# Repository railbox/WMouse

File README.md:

## Introduction
This is the Open Sourse WiFi DCC remote control for controlling turnouts and locomotives via command stations supporting Roco Z21 Wi-Fi protocol. 
The hardware is based on ESP8266 chip and ssd1106 based OLED.
The software is using Arduino IDE for output hex file building.
### Dependensies
The code dependant on ESP8266 library for Arduino IDE and Async UDP Library for ESP8266 Arduino.
### Helpers
There is a possibility to debug device menu using CodeBlocks IDE on the Windows. See Menu.cbp.

## Configuration
User should configure the default Wi-Fi net name and password in "src/config.h" file. See CL_SSID and CL_PASS defines.

## Hardware
The PCB project made in Kicad IDE could be fould under Mouse folder.
The PCB thickness is 1mm.
The case is borrowed from airconditioner remote control DG11J1-16 which could be found on aliexpress or ebay.

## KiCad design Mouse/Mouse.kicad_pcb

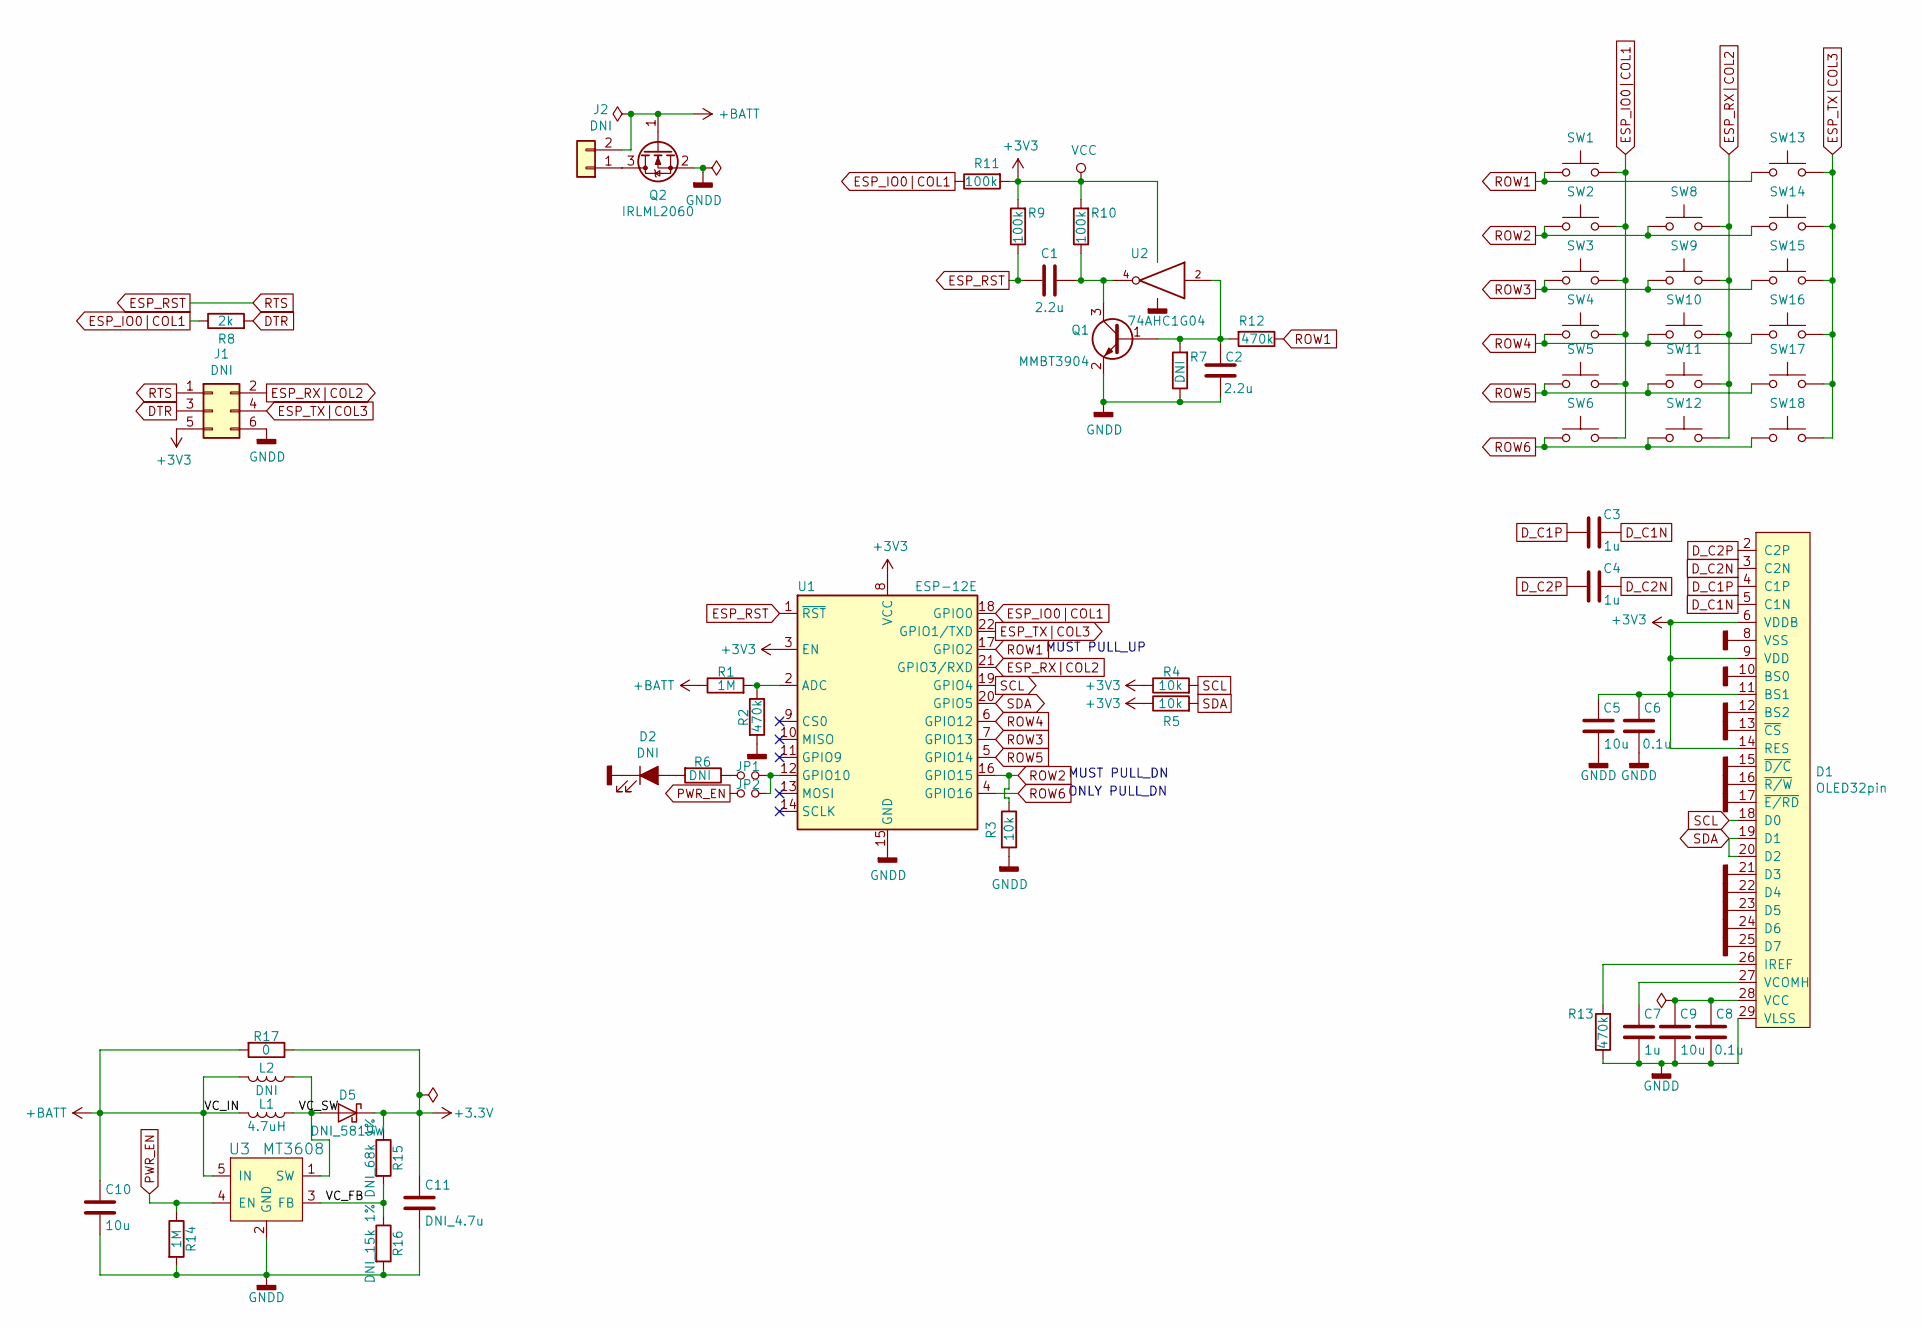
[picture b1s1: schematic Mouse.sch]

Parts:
C1, C2: 2.2u; C_0805_2012Metric_Pad1.15x1.40mm_HandSolder
C3, C4, C7: 1u; C_0805_2012Metric_Pad1.15x1.40mm_HandSolder
C5, C9, C10: 10u; C_0805_2012Metric_Pad1.15x1.40mm_HandSolder
C6, C8: 0.1u; C_0805_2012Metric_Pad1.15x1.40mm_HandSolder
C11: DNI_4.7u; C_0805_2012Metric_Pad1.15x1.40mm_HandSolder
D1: OLED32pin; OLED_32pin
D2: DNI; LED_D5.0mm_Horizontal_O3.81mm_Z3.0mm
D5: DNI_5819W; D_SOD-123
J1: DNI; PinHeader_2x03_P2.54mm_Vertical
J2: DNI; RC_case
JP1, JP2: DNI; SolderJumper-2_P1.3mm_Open_TrianglePad1.0x1.5mm
L1: 4.7uH; L_1210_3225Metric_Pad1.42x2.65mm_HandSolder
L2: DNI; L_1812_4532Metric
Q1: MMBT3904; SOT-23_Handsoldering
Q2: IRLML2060; SOT-23_Handsoldering
R1, R14: 1M; R_0805_2012Metric_Pad1.15x1.40mm_HandSolder
R2, R12, R13: 470k; R_0805_2012Metric_Pad1.15x1.40mm_HandSolder
R3, R4, R5: 10k; R_0805_2012Metric_Pad1.15x1.40mm_HandSolder
R6, R7: DNI; R_0805_2012Metric_Pad1.15x1.40mm_HandSolder
R8: 2k; R_0805_2012Metric_Pad1.15x1.40mm_HandSolder
R9, R10, R11: 100k; R_0805_2012Metric_Pad1.15x1.40mm_HandSolder
R15: DNI_68k 1%; R_0805_2012Metric_Pad1.15x1.40mm_HandSolder
R16: DNI_15k 1%; R_0805_2012Metric_Pad1.15x1.40mm_HandSolder
R17: 0; R_0805_2012Metric_Pad1.15x1.40mm_HandSolder
SW1: DNI_PCB; RC_button_long
SW2, SW3, SW4, SW5, SW6, SW8, SW9, SW10, SW11, SW12, SW13, SW14, SW15, SW16, SW17, SW18: DNI_PCB; RC_button
U1: ESP-12E
U2: 74AHC1G04; SOT-23-5_HandSoldering
U3: MT3608; SOT-23-6

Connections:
+BATT: C10.1, J2.2, L1.2, L2.2, Q2.1 (G), R1.1, R17.2, U3.5 (IN)
/VC_FB: R15.2, R16.1, U3.3 (FB)
/VC_SW: D5.2 (A), L1.1, L2.1, U3.1 (SW)
DTR: J1.3, R8.2
D_C1N: C3.1, D1.5 (C1N)
D_C1P: C3.2, D1.4 (C1P)
D_C2N: C4.1, D1.3 (C2N)
D_C2P: C4.2, D1.2 (C2P)
ESP_IO0|COL1: R8.1, R11.1, SW1.2, SW2.2, SW3.2, SW4.2, SW5.2, SW6.2, U1.18 (GPIO0)
ESP_RST: C1.1, J1.1, R9.1, U1.1 (~RST)
ESP_RX|COL2: J1.2, SW8.2, SW9.2, SW10.2, SW11.2, SW12.2, U1.21 (GPIO3/RXD)
ESP_TX|COL3: J1.4, SW13.2, SW14.2, SW15.2, SW16.2, SW17.2, SW18.2, U1.22 (GPIO1/TXD)
GND: C2.1, C5.1, C6.1, C7.1, C8.1, C9.1, C10.2, C11.2, D1.8 (VSS), D1.10 (BS0), D1.12 (BS2), D1.13 (~CS), D1.15 (~D/C), D1.16 (~R/W), D1.17 (~E/RD), D1.21 (D3), D1.22 (D4), D1.23 (D5), D1.24 (D6), D1.25 (D7), D1.29 (VLSS), D2.1 (K), J1.6, Q1.2 (E), Q2.2 (S), R2.2, R3.2, R7.1, R13.1, R14.2, R16.2, U1.15 (GND), U2.3 (GND), U3.2 (GND)
unnamed: C1.2, Q1.3 (C), R10.1, U2.4
unnamed: C2.2, Q1.1 (B), R7.2, R12.2, U2.2
unnamed: C7.2, D1.27 (VCOMH)
unnamed: C8.2, C9.2, D1.28 (VCC)
unnamed: D1.26 (IREF), R13.2
unnamed: D2.2 (A), R6.2
unnamed: J2.1, Q2.3 (D)
unnamed: JP1.1, R6.1
unnamed: JP1.2, JP2.2, U1.12 (GPIO10)
unnamed: R1.2, R2.1, U1.2 (ADC)
PWR_EN: JP2.1, R14.1, U3.4 (EN)
ROW1: R12.1, SW1.1, SW13.1, U1.17 (GPIO2)
ROW2: R3.1, SW2.1, SW8.1, SW14.1, U1.16 (GPIO15)
ROW3: SW3.1, SW9.1, SW15.1, U1.7 (GPIO13)
ROW4: SW4.1, SW10.1, SW16.1, U1.6 (GPIO12)
ROW5: SW5.1, SW11.1, SW17.1, U1.5 (GPIO14)
ROW6: SW6.1, SW12.1, SW18.1, U1.4 (GPIO16)
SCL: D1.18 (D0), R4.2, U1.19 (GPIO4)
SDA: D1.19 (D1), D1.20 (D2), R5.2, U1.20 (GPIO5)

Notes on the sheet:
MUST PULL_UP
MUST PULL_DN
ONLY PULL_DN

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
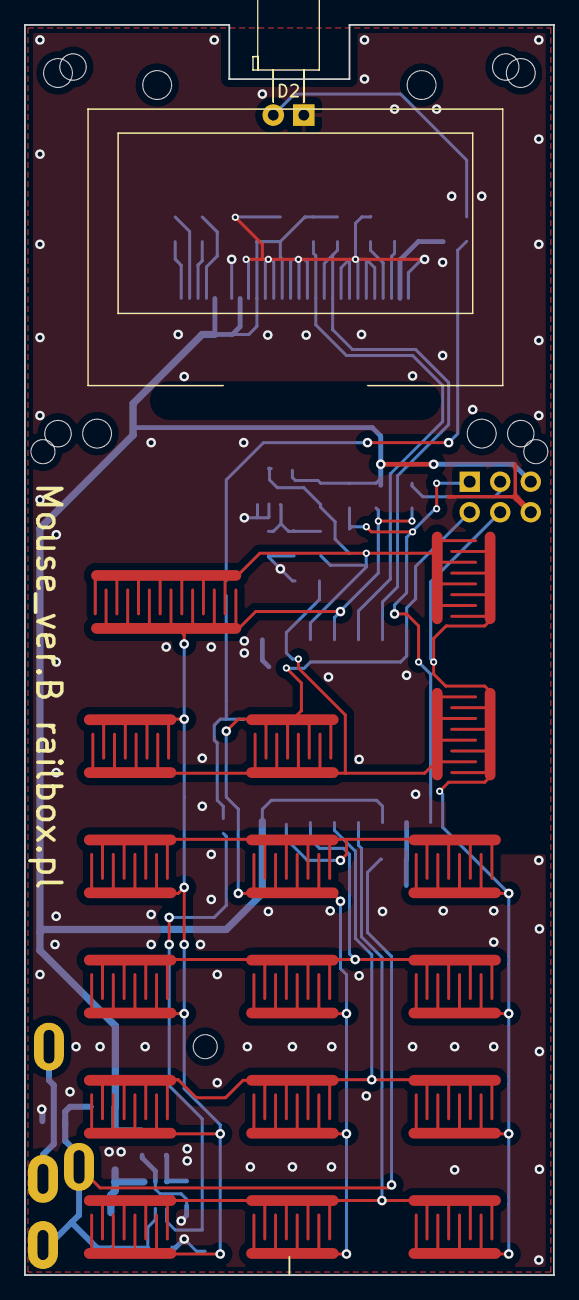
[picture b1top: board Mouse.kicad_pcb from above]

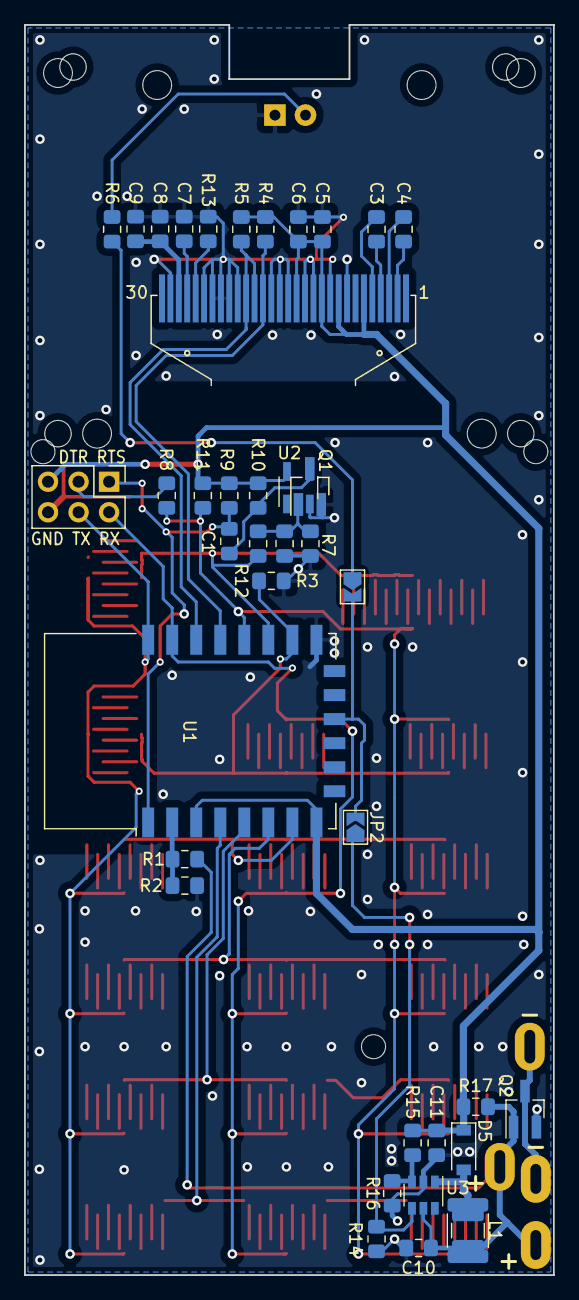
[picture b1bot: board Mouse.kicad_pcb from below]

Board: 2 copper layers, 44.0 x 104.0 mm, 59 parts (39 on the bottom side), 33 nets.

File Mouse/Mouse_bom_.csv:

"sep=,"
Component,Description,References,Value,Footprint,Quantity Per PCB
1,Unpolarized capacitor,C6 C8,0.1u,C_0805_2012Metric_Pad1.15x1.40mm_HandSolder,2
2,Unpolarized capacitor,C5 C9-C10,10u,C_0805_2012Metric_Pad1.15x1.40mm_HandSolder,3
3,Unpolarized capacitor,C3-C4 C7,1u,C_0805_2012Metric_Pad1.15x1.40mm_HandSolder,3
4,Unpolarized capacitor,C1-C2,2.2u,C_0805_2012Metric_Pad1.15x1.40mm_HandSolder,2
5,,D1,OLED32pin,OLED_32pin,1
6,Inductor,L1,4.7uH,L_1210_3225Metric_Pad1.42x2.65mm_HandSolder,1
7,"50V Vds, 0.22A Id, N-Channel MOSFET, SOT-23",Q2,IRLML2060,SOT-23_Handsoldering,1
8,"0.8A Ic, 45V Vce, NPN Transistor, SOT-23",Q1,MMBT3904,SOT-23_Handsoldering,1
9,Resistor,R17,0,R_0805_2012Metric_Pad1.15x1.40mm_HandSolder,1
10,Resistor,R9-R11,100k,R_0805_2012Metric_Pad1.15x1.40mm_HandSolder,3
11,Resistor,R3-R5,10k,R_0805_2012Metric_Pad1.15x1.40mm_HandSolder,3
12,Resistor,R1 R14,1M,R_0805_2012Metric_Pad1.15x1.40mm_HandSolder,2
13,Resistor,R8,2k,R_0805_2012Metric_Pad1.15x1.40mm_HandSolder,1
14,Resistor,R2 R12-R13,470k,R_0805_2012Metric_Pad1.15x1.40mm_HandSolder,3
15,"Single NOT Gate, Low-Voltage CMOS",U2,74AHC1G04,SOT-23-5_HandSoldering,1
16,802.11 b/g/n Wi-Fi Module,U1,ESP-12E,ESP-12E,1
17,"DC-DC Step-up converter, constant frequency, 6-pin SOT23",U3,MT3608,SOT-23-6,1





Component Groups:,17
Component Count:,30
Fitted Components:,30
Number of PCBs:,1
Total components:,30
Schematic Version:,
Schematic Date:,
BoM Date:,18.09.2020 15:21:41
Schematic Source:,C:\Users\Toxa\YandexDisk\PROGRAMMING\Modules_with_MCU\WMouse\_hardware\Mouse\Mouse.sch
KiCad Version:,Eeschema (5.1.5)-3

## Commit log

2020-09-18 Add source files
2020-09-18 Add hardware files
2020-12-08 Fix bug with maximum speed and increase loco speed steps
2021-03-29 Add continious loco speed increase. Restor last turnout state
